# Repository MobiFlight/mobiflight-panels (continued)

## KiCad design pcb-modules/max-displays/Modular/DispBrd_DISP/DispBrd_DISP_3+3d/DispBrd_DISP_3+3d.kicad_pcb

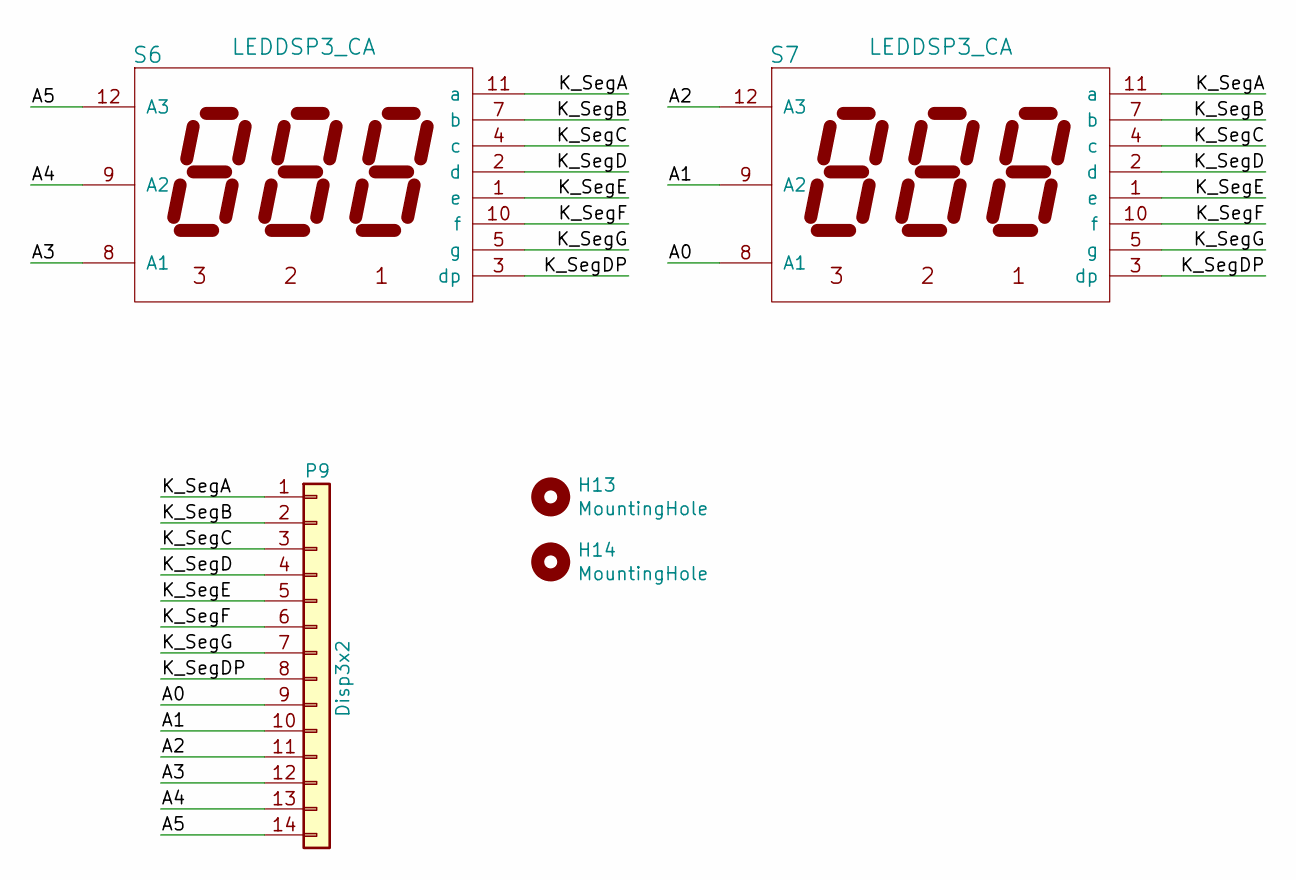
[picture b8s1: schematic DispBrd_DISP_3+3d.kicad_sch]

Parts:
H13, H14: MountingHole; Hole3mm
P9: Disp3x2; IDC-Header_2x07_P2.54mm_Vertical
S6, S7: LEDDSP3_CA; Disp7s3x_036

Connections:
/A0: P9.9, S7.8 (A1)
/A1: P9.10, S7.9 (A2)
/A2: P9.11, S7.12 (A3)
/A3: P9.12, S6.8 (A1)
/A4: P9.13, S6.9 (A2)
/A5: P9.14, S6.12 (A3)
/K_SegA: P9.1, S6.11 (a), S7.11 (a)
/K_SegB: P9.2, S6.7 (b), S7.7 (b)
/K_SegC: P9.3, S6.4 (c), S7.4 (c)
/K_SegD: P9.4, S6.2 (d), S7.2 (d)
/K_SegDP: P9.8, S6.3 (dp), S7.3 (dp)
/K_SegE: P9.5, S6.1 (e), S7.1 (e)
/K_SegF: P9.6, S6.10 (f), S7.10 (f)
/K_SegG: P9.7, S6.5 (g), S7.5 (g)

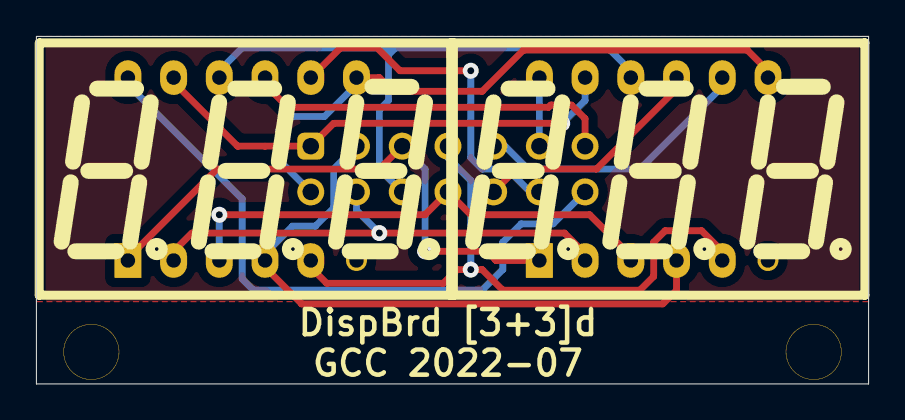
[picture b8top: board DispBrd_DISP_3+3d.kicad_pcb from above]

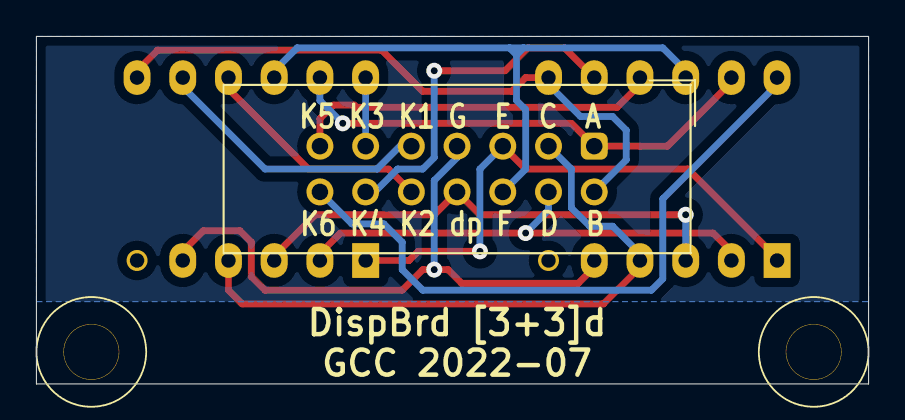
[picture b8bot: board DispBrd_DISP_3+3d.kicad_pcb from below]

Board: 2 copper layers, 46.2 x 19.3 mm, 5 parts (3 on the bottom side), 14 nets.

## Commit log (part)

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2021-07-24 adjusted tape mask to be symmetric
2021-07-25 added lights panel
2021-07-26 adjusted holes slightly to match pcb design
2021-07-27 enlarged the selector knob hole a bit
2021-07-29 added pcb design and updated panel
2021-07-29 added 3d printable mechanism
2021-08-02 Split top panel display cutout back into two pieces to match the real Airbus FCU
2021-08-02 added generic com radio panel (I thought I had already added this..)
2021-08-02 fixed some accidental 'stroke to path' rounded rectangles on buttons that would not cut on laser
2021-08-03 Updated light rings to use consistent size for all four knobs
2021-08-03 Removed cut to the right of the ALT indicator to better follow the underlying PCB design (and both the ALT and LVL/CH text always follow their lit state)
2021-08-06 Reverted to 14.7mm for 14mm knob skirt after testing variant. This version has less notable wobble in practice.
2021-08-11 added unfinished left EFIS panel by Bummelfuchs
2021-08-14 rounded the sharp corners
2021-08-15 Changed round button cutouts to 10.200mm (10mm for cap + 0.2mm for spacing)
2021-08-21 Numerous adjustments for the final version
2021-08-21 Adding schematic and PCB. Still needs a true BOM as the one built into the design here will be lacking some of the components, the Push-Pull encoder mechanism, for example.
2021-08-23 Updated a screw location that was close to edge
    Testing upload via browser also,
    But this is a new version from MadMonkeyFPV that fixes one screw hole that was rather close to the panel edge.
2021-08-25 added small rectangular holes to account for small tabs on the potentiometers
2021-08-29 added paint mask to hopefully block light between indicator leds and backlight
2021-08-29 added pcb design files for easyeda & mobiflight config files for msfs2020
2021-08-29 updated some stuff, still not finished
2021-08-29 Cleaned up names of EasyEDA JSON files
2021-08-30 updated MF config files for cj4 electric panel
2021-08-31 Added comment about this repo being a work in progress.
2021-09-01 Removed old EasyEDA JSON files that were replaced with last rename action
2021-09-01 initial readme, continue edit in web view
2021-09-01 added pcb files as well as adjusted the bottom panel to add slots for the potentiometer alignment tabs
2021-09-01 added pcb for lights panel
2021-09-02 aligned holes and button labels
2021-09-02 moved buttons more to center to make the arduino fit better
2021-09-03 work in progress of the A320 overhead.
2021-09-03 added TBM930 autopilot panel (work in progress)
2021-09-05 Fixed incorrect LCD module wiring in the rightmost module of the PCB (version 1.0.2).
2021-09-07 updated standoff hole locations to match upcoming pcb designs
2021-09-10 Added Korry Switch STLs
2021-09-10 Updated FCU readme markdown
2021-09-10 added pcb for pfd menu panel
2021-09-10 added the mobiflight configuration files
2021-09-14 Added docs for electronics part list and clarified switches used for round buttons for the panel within the schematic
2021-09-14 oops one panel cutout had moved, fixing
2021-09-14 added split panels
2021-09-14 added the right column separate panels
2021-09-15 Changed BARO to BFE and added PCB outline
2021-09-16 Added variant of the panel SVG that supports a smaller PCB
2021-09-17 Update README.md
    Fixed phrasing that made it clearer the mentioned bodge has been fixed and was only present in an older version.
2021-09-24 Version 1.0 of the EFIS Panel (Left)
2021-09-24 Update README.md
    Fixed typo
2021-09-26 Fixed issue with upper panel Korry cutouts using fill in lieu of stroke (would prevent K40 whisperer from recognizing it as a cut path. Added outer mask for lower panel layer.
2021-09-27 Fixed surface interface for B3F-105X switch on Korry switch
2021-09-28 Adjusted FCU knob 3D models for a better fit. Removed old models that had a void that should not have been present.
2021-09-29 tweaked the cabin altitude scale
    Made the cabin altitude range to match the sim overhead.
2021-09-29 Fixes TLC5917IN latch pins not being wired up to the Arduino
2021-09-30 Increased the lower panel diameter for the SR16 rotary switches to 16mm. This also eliminates the need to trim the tab off to fit correctly.
2021-10-01 Revert "Fixes TLC5917IN latch pins not being wired up to the Arduino"
    This reverts commit 88a111a7ac717a5f2666d54f864e8e079452b599.
2021-10-01 Minor adjustment to align the BARO knob with the PCB.
2021-10-02 renamed electrical panel config files, updated landing gear panel 3d printable files
2021-10-09 Added right (F.O.) EFIS PCB and SVG design.
2021-10-10 Removed duplicate objects and minor adjustments to layout
2021-10-10 Fixed missing hole for bottom panel. Removed engraving from outline of Signs "Korry" (this is not a pressable button), and the outline isn't present in MSFS2020 nor A320 cockpit pictures. Added butto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
2021-10-23 Added A320 pedestal ECAM panel
2021-10-26 Added initial Landing Gear Status panel for the A320 MIP
2021-10-27 Added initial SVG for A320 digital chrono
2021-10-28 Added initial A320 illumination panel
2021-10-29 Added the FCU MobiFlight configuration files
2021-10-30 Various adjustments to the Landing Gear Status panel for the Airbus A320 MIP
2021-10-31 Additional tweaks to landing gear status to facilitate MIP mounting
2021-10-31 Added top-bottom panel screws for digit chrono. Added mounting edge for MIP
2021-10-31 Adjusted holes on bottom panel for more strength on MIP mounting
2021-10-31 Added MAX7219 display designs by GioCC
2021-11-01 Added alternate version of the A320 landing gear lever
2021-11-03 Rename aircraft/airbus-a32x/main-instrument-panel/efis/A32x-efis-left.svg to aircraft/airbus-a32x/glareshield/efis/A32x-efis-left.svg
2021-11-03 Rename aircraft/airbus-a32x/main-instrument-panel/efis/A32x-efis-right.svg to aircraft/airbus-a32x/glareshield/efis/A32x-efis-right.svg
2021-11-03 Rename aircraft/airbus-a32x/main-instrument-panel/landing-gear-status/a32x-landing-gear-status.svg to aircraft/airbus-a32x/main-instrument-panel/autobrake/a32x-autobrake.svg
2021-11-03 Rename aircraft/airbus-a32x/main-instrument-panel/landing-gear-status/README.md to aircraft/airbus-a32x/main-instrument-panel/autobrake/README.md
2021-11-08 Fixed issues identified during laser cutting. Specifically, the Korry cutouts on the top layer were showing up as raster elements in K40 Whisperer.
2021-11-08 Removed superfluous Bottom Panel Cutout layer.
2021-11-08 Updated label and ON BATT Korry to match alignment of middle Korrys
2021-11-10 Update README.md
    Fixed typos
2021-11-10 Completed initial design of the Autobrake Panel and corresponding PCB.
2021-11-12 Added A320 Illumination panel PCB
2021-11-12 Cleaned up A320 autobrake PCB silkscreen
2021-11-12 Added header for extra pins to A320 Illumination panel
2021-11-15 Added resin-printable version
    The resin printers have high enough resolution that you can create threads for a set screw. Might need a light cleanup with a M3 thread tapping tool.
2021-11-18 Added connectors for Switching Panel
2021-11-18 Added stress relief for power barrel jack
2021-11-21 Create README.md and ground services folder
    Working via the web interface to make folders
2021-11-25 Moved APU input from D13 to D25 to avoid built-in LED issue.
2021-11-26 Swapped VCC and GND on pots so full CCW represents low value in MobFlight.
2021-12-03 Updated documentation for v1.0 of the A320 Autobrake Panel to indicate it has been tested.
2021-12-05 added (work in progress) 737 style transponder panel
2021-12-07 Added paint mask to swtich
2021-12-07 Added tape mask to PFD/ND XFR button
2021-12-10 Added A320 Brake Pressure panel
2021-12-12 Add files via upload
    grouped stl files for ordering through JLCPCB to minimise cost
2021-12-18 Derived an STL from the laser cutting SVG, based on a layer height of 3mm
2021-12-19 Create Flood light panel
2021-12-19 Rename TCAS to TCAS.svg
    Renamed file so GitHub will properly recognize and format contents.
2021-12-19 Rename aircraft/airbus-a32x/pedestal/Flood light panel.svg to aircraft/airbus-a32x/pedestal/flood-light/Flood light panel.svg
    Moved to own subfolder
2021-12-19 Rename aircraft/airbus-a32x/pedestal/TCAS.svg to aircraft/airbus-a32x/pedestal/atc-tcas/ATC-TCAS.svg
    Moved to own subfolder
2021-12-26 updated mvf menu panel, buttons for more spacing to match pcb
2021-12-26 update custom long press event for mfd data rotary push, it has long press event too
2021-12-27 added photo to readme
    added photo to readme
2021-12-27 centered buttons on panel (oops) and adjusted pcb layout, also added a centered panel file for my remaining old pcb batch that centers the buttons
2021-12-31 Created folder structure to store common files, such as STLs used by multiple panels.
2021-12-31 Updated FCU readme file to reference common folder structure for Korrys
2021-12-31 Added annunciator-only Korry 389
2022-01-05 Add files via upload
    added congiguration files for the arduino's and for MF to save users having to do it manually button by button
2022-01-14 move screw holes 3mm inwards to fit 3D-printed support
2022-01-15 added missing A320 MCDU button caps
2022-01-17 oops top panel was missing the gear handle hole
2022-01-18 Added MobiFlight config files for A320 EFIS Panel
2022-01-18 Added MobiFlight config files for A320 Autobrake Panel
2022-01-18 Added the A320 Mini Overhead Panel
2022-01-25 adjust the height of the support piece
2022-02-01 Added EasyEDA json sources
2022-02-07 Incorporated CmdrJk's fix to the MCDU STL in which the screen bezel was protruding into the right line-select keys.
2022-02-12 Updated datasheet URL to point to the correct part for 2281AG
2022-02-28 Added A320 Warning Panel
2022-02-28 Fix typo in Mini Overhead
2022-03-12 Update Mini Overhead readme to include reference to ADIRS knob STL
2022-03-12 Delete letter_button.stl
    replaced by updated version
2022-03-12 Create readme.md
    Basic info for button caps
2022-03-12 Update readme.md
    basic info added
2022-03-12 Update readme.md
    Updated To-Do and link to panel svg source file.
2022-04-25 Fix typos
2022-05-16 Added analog panel files form WhiteKnuckle
2022-06-03 added alt version where switch nut and washer is hidden below top panel
2022-06-03 added anti-ice panel for CJ4
2022-07-03 added a simple 8 button panel for KD2 switches and single navcom (no pcb for that yet)
2022-07-03 added readme to KD2 panel
2022-11-29 Update README.md
    ### Status: **Complete** - The current PCB (v1.0.3) has been fabricated and tested.
2022-12-04 Added cabin climb gauge background svg
2022-12-05 added work in progress overhead panel set and frame
2022-12-05 added overhead frame and some gauge designs
2022-12-13 Added assembly image, cleaned up the panels etc from this as they are to be created on separate files
2022-12-22 first version of first panel of first column :)
2022-12-26 added flaps gauge svg
2023-01-24 updated apu egt and flaps gauge with pointers out of way, added cabin altimater
2023-01-24 Folder for GA instruments created
2023-02-10 Fix issue with managed dashes used in Comparison
2023-02-28 added A320 parking brake handle
2023-05-31 Initial working version of A320 Digitial Chrono panel
2023-06-09 Adjust position of bottom-right rotary for easier mounting
2023-07-04 Initial work on A320 transponder panel (ATC-TCAS)
2023-08-01 had a newer version on my disk, but unfortunately I dont remember what is changed
2023-08-17 H145 Overhead Panel
    Airbus H145 Overhead Panel
2023-08-17 Move H145 overhead into the appropriate subfolder
2023-09-01 this is very out of date, will replace with a newer one.
2023-09-24 Fix asset links in A320 ATC-TCAS readme
2023-10-15 Update 389 Korry to use larger light channels
2023-10-16 Create README.md for analog gaugfes folder
2023-10-16 added simple styleguide for naming conventions
2023-10-16 added the graphics files via web interface
2023-10-16 Add C172 Airspeed VSpeed Attitude gfx
    Added C172 airspeed, vertical speed, and attitude indicator graphics.
2023-10-16 Readme image embeds
2023-11-14 Create svg
2023-11-28 Add files via upload
    parking brake mechanism
2023-11-30 Create file
2023-12-22 Create avionics
2023-12-26 Add files via upload
    based from A320_MCDU-laser.svg, this is a fusion360 3d model of MCDU smd pcb housing with base features hinge and handle.
2023-12-28 OVH-1st-batch
2023-12-29 Added STEP file for the mcdu panel with handle
    This is STEP so it can be edited in other apps than F360, like FreeCAD.
    File is also from @iamSiiN
2025-11-11 Add Boeing 737NG main instrument panel (MIP) base panel for laser cutout
